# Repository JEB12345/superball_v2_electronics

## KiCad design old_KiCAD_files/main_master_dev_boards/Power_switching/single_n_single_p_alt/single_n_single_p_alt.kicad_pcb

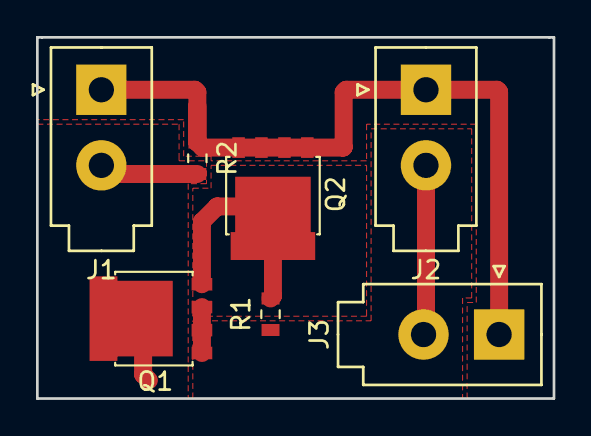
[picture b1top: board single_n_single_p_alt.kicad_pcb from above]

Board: 2 copper layers, 28.7 x 20.1 mm, 7 parts (0 on the bottom side), 4 nets.

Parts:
J1: Batt_in; Molex_MiniFit-JR-5556-02A_2x01x4.20mm_Straight
J2: Ext_in; Molex_MiniFit-JR-5556-02A_2x01x4.20mm_Straight
J3: Out; Molex_MiniFit-JR-5556-02A_2x01x4.20mm_Straight
Q1: RQ3E120ATTB; SOT-669_LFPAK
Q2: PSMN013-80YS; SOT-669_LFPAK
R1: 100k; R_0603_1608Metric
R2: 200k; R_0603_1608Metric

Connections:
GND: J1.1, J2.1, J3.1, Q2.1, Q2.2, Q2.3, Q2.4, R2.1
unnamed: J1.2, Q1.1, Q1.2, Q1.3, R2.2
unnamed: J2.2, J3.2, Q1.5, R1.1
unnamed: Q1.4, Q2.5, R1.2
